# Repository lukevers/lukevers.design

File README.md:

# lukevers.design

There isn't a ton here right now. Feel free to poke around, but best to come back later.

✨

## Project Structure

Each project in [projects](./projects) should have a `manifest.json` that defines everything about the project. This data will be consumed on boot by the backend server, and be available via API for the frontend to consume.

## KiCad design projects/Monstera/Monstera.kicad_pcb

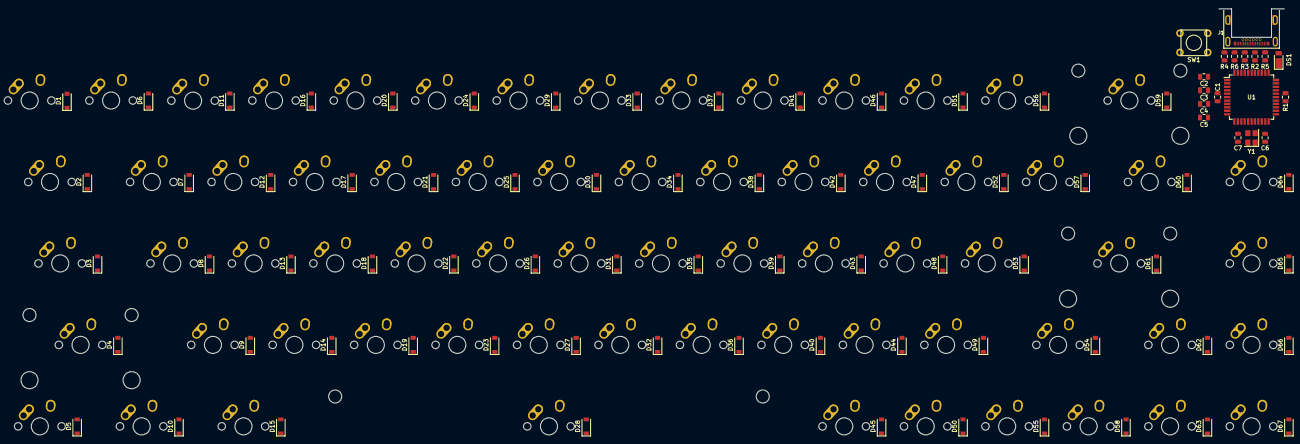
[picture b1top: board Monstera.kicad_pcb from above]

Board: 2 copper layers, 152 parts (0 on the bottom side), 100 nets, no tracks yet.

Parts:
C1: 1uF; C_0805_2012Metric
C2: 10uF; C_0805_2012Metric
C3, C4, C5: 0.1uF; C_0805_2012Metric
C6, C7: 22pF; C_0805_2012Metric
D1, D2, D3, D4, D5, D6, D7, D8, D9, D10, D11, D12, D13, D14, D15, D16, D17, D18, D19, D20, D21, D22, D23, D24, D25, D26, D27, D28, D29, D30, D31, D32, D33, D34, D35, D36, D37, D38, D39, D40, D41, D42, D43, D44, D45, D46, D47, D48, D49, D50, D51, D52, D53, D54, D55, D56, D57, D58, D59, D60, D61, D62, D63, D64, D65, D66, D67: D_Small; D_SOD-123
DS1: D_Schottky_Small; D_PowerDI-123
J1: USB_C_Receptacle; CX70M-24P1
MX_1, MX_2, MX_3, MX_4, MX_5, MX_6, MX_7, MX_8, MX_9, MX_10: MX-NoLED; MX-1U-NoLED
MX_A1: MX-NoLED; MX-1U-NoLED
MX_B1: MX-NoLED; MX-1U-NoLED
MX_BACKSPACE1: MX-NoLED; MX-2U-NoLED
MX_C1: MX-NoLED; MX-1U-NoLED
MX_COLON1: MX-NoLED; MX-1U-NoLED
MX_COMMA1: MX-NoLED; MX-1U-NoLED
MX_CTRL1: MX-NoLED; MX-1.25U-NoLED
MX_D1: MX-NoLED; MX-1U-NoLED
MX_DASH1: MX-NoLED; MX-1U-NoLED
MX_DOWN1: MX-NoLED; MX-1U-NoLED
MX_E1: MX-NoLED; MX-1U-NoLED
MX_ENTER1: MX-NoLED; MX-2.25U-NoLED
MX_ESC1: MX-NoLED; MX-1U-NoLED
MX_F1: MX-NoLED; MX-1U-NoLED
MX_FN1: MX-NoLED; MX-1U-NoLED
MX_G1: MX-NoLED; MX-1U-NoLED
MX_H1: MX-NoLED; MX-1U-NoLED
MX_HOME1: MX-NoLED; MX-1U-NoLED
MX_I1: MX-NoLED; MX-1U-NoLED
MX_J1: MX-NoLED; MX-1U-NoLED
MX_K1: MX-NoLED; MX-1U-NoLED
MX_L1: MX-NoLED; MX-1U-NoLED
MX_LALT1: MX-NoLED; MX-1.25U-NoLED
MX_LBRACE1: MX-NoLED; MX-1U-NoLED
MX_LEFT1: MX-NoLED; MX-1U-NoLED
MX_LMETA1: MX-NoLED; MX-1.25U-NoLED
MX_LOCK1: MX-NoLED; MX-1.75U-NoLED
MX_LSHIFT1: MX-NoLED; MX-2.25U-NoLED
MX_M1: MX-NoLED; MX-1U-NoLED
MX_N1: MX-NoLED; MX-1U-NoLED
MX_O1: MX-NoLED; MX-1U-NoLED
MX_P1: MX-NoLED; MX-1U-NoLED
MX_PERIOD1: MX-NoLED; MX-1U-NoLED
MX_PGDN1: MX-NoLED; MX-1U-NoLED
MX_PGUP1: MX-NoLED; MX-1U-NoLED
MX_PIPE1: MX-NoLED; MX-1.5U-NoLED
MX_PLUS1: MX-NoLED; MX-1U-NoLED
MX_Q1: MX-NoLED; MX-1U-NoLED
MX_QUEST1: MX-NoLED; MX-1U-NoLED
MX_QUOTE1: MX-NoLED; MX-1U-NoLED
MX_R1: MX-NoLED; MX-1U-NoLED
MX_RALT1: MX-NoLED; MX-1U-NoLED
MX_RBRACE1: MX-NoLED; MX-1U-NoLED
MX_RIGHT1: MX-NoLED; MX-1U-NoLED
MX_RMETA1: MX-NoLED; MX-1U-NoLED
MX_RSHIFT1: MX-NoLED; MX-1.75U-NoLED
MX_S1: MX-NoLED; MX-1U-NoLED
MX_SPACE1: MX-NoLED; MX-6.25U-NoLED
MX_T1: MX-NoLED; MX-1U-NoLED
MX_TAB1: MX-NoLED; MX-1.5U-NoLED
MX_U1: MX-NoLED; MX-1U-NoLED
MX_UP1: MX-NoLED; MX-1U-NoLED
MX_V1: MX-NoLED; MX-1U-NoLED
MX_W1: MX-NoLED; MX-1U-NoLED
MX_X1: MX-NoLED; MX-1U-NoLED
MX_Y1: MX-NoLED; MX-1U-NoLED
MX_Z1: MX-NoLED; MX-1U-NoLED
R1, R4: 10k; R_0805_2012Metric
R2, R3: 22; R_0805_2012Metric
R5, R6: 5k1; R_0805_2012Metric
SW1: SW_Push; PushButton_6x6mm_TH
U1: ATmega32U4-AU; TQFP-44_10x10mm_P0.8mm
Y1: 16MHz; Crystal_SMD_3225-4Pin_3.2x2.5mm

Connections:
+5V: C2.1, C3.1, C4.1, C5.1, R4.1, U1.2, U1.7, U1.14, U1.24, U1.34, U1.44
COL0: MX_CTRL1.1, MX_ESC1.1, MX_LOCK1.1, MX_LSHIFT1.1, MX_TAB1.1
COL1: MX_1.1, MX_A1.1, MX_LALT1.1, MX_Q1.1, MX_Z1.1
COL2: MX_2.1, MX_LMETA1.1, MX_S1.1, MX_W1.1, MX_X1.1
COL3: MX_3.1, MX_C1.1, MX_D1.1, MX_E1.1
COL4: MX_4.1, MX_F1.1, MX_R1.1, MX_V1.1
COL5: MX_5.1, MX_B1.1, MX_G1.1, MX_SPACE1.1, MX_T1.1
COL6: MX_6.1, MX_H1.1, MX_N1.1, MX_Y1.1
COL7: MX_7.1, MX_J1.1, MX_M1.1, MX_U1.1
COL8: MX_8.1, MX_COMMA1.1, MX_I1.1, MX_K1.1, MX_RMETA1.1
COL9: MX_9.1, MX_L1.1, MX_O1.1, MX_PERIOD1.1, MX_RALT1.1
COL10: MX_10.1, MX_COLON1.1, MX_FN1.1, MX_P1.1, MX_QUEST1.1
COL11: MX_DASH1.1, MX_LBRACE1.1, MX_LEFT1.1, MX_QUOTE1.1, MX_RSHIFT1.1
COL12: MX_DOWN1.1, MX_ENTER1.1, MX_PLUS1.1, MX_RBRACE1.1, MX_UP1.1
COL13: MX_BACKSPACE1.1, MX_HOME1.1, MX_PGDN1.1, MX_PGUP1.1, MX_PIPE1.1, MX_RIGHT1.1
GND: C1.2, C2.2, C3.2, C4.2, C5.2, C6.2, C7.2, J1.A1, J1.A12, J1.B1, J1.B12, J1.S1, R1.1, R5.1, R6.1, SW1.1, U1.5, U1.15, U1.23, U1.35, U1.43, Y1.2, Y1.4
unnamed: C1.1, U1.6
unnamed: C6.1, U1.17, Y1.1
unnamed: C7.1, U1.16, Y1.3
unnamed: D1.2, MX_ESC1.2
unnamed: D2.2, MX_TAB1.2
unnamed: D3.2, MX_LOCK1.2
unnamed: D4.2, MX_LSHIFT1.2
unnamed: D5.2, MX_CTRL1.2
unnamed: D6.2, MX_1.2
unnamed: D7.2, MX_Q1.2
unnamed: D8.2, MX_A1.2
unnamed: D9.2, MX_Z1.2
unnamed: D10.2, MX_LALT1.2
unnamed: D11.2, MX_2.2
unnamed: D12.2, MX_W1.2
unnamed: D13.2, MX_S1.2
unnamed: D14.2, MX_X1.2
unnamed: D15.2, MX_LMETA1.2
unnamed: D16.2, MX_3.2
unnamed: D17.2, MX_E1.2
unnamed: D18.2, MX_D1.2
unnamed: D19.2, MX_C1.2
unnamed: D20.2, MX_4.2
unnamed: D21.2, MX_R1.2
unnamed: D22.2, MX_F1.2
unnamed: D23.2, MX_V1.2
unnamed: D24.2, MX_5.2
unnamed: D25.2, MX_T1.2
unnamed: D26.2, MX_G1.2
unnamed: D27.2, MX_B1.2
unnamed: D28.2, MX_SPACE1.2
unnamed: D29.2, MX_6.2
unnamed: D30.2, MX_Y1.2
unnamed: D31.2, MX_H1.2
unnamed: D32.2, MX_N1.2
unnamed: D33.2, MX_7.2
unnamed: D34.2, MX_U1.2
unnamed: D35.2, MX_J1.2
unnamed: D36.2, MX_M1.2
unnamed: D37.2, MX_8.2
unnamed: D38.2, MX_I1.2
unnamed: D39.2, MX_K1.2
unnamed: D40.2, MX_COMMA1.2
unnamed: D41.2, MX_9.2
unnamed: D42.2, MX_O1.2
unnamed: D43.2, MX_L1.2
unnamed: D44.2, MX_PERIOD1.2
unnamed: D45.2, MX_RMETA1.2
unnamed: D46.2, MX_10.2
unnamed: D47.2, MX_P1.2
unnamed: D48.2, MX_COLON1.2
unnamed: D49.2, MX_QUEST1.2
unnamed: D50.2, MX_RALT1.2
unnamed: D51.2, MX_DASH1.2
unnamed: D52.2, MX_LBRACE1.2
unnamed: D53.2, MX_QUOTE1.2
unnamed: D54.2, MX_RSHIFT1.2
unnamed: D55.2, MX_FN1.2
unnamed: D56.2, MX_PLUS1.2
unnamed: D57.2, MX_RBRACE1.2
unnamed: D58.2, MX_LEFT1.2
unnamed: D59.2, MX_BACKSPACE1.2
unnamed: D60.2, MX_PIPE1.2
unnamed: D61.2, MX_ENTER1.2
unnamed: D62.2, MX_UP1.2
unnamed: D63.2, MX_DOWN1.2
unnamed: D64.2, MX_HOME1.2
unnamed: D65.2, MX_PGUP1.2
unnamed: D66.2, MX_PGDN1.2
unnamed: D67.2, MX_RIGHT1.2
unnamed: J1.A5, R5.2
unnamed: J1.A6, J1.B6, R2.2
unnamed: J1.A7, J1.B7, R3.2
unnamed: J1.B5, R6.2
unnamed: R1.2, U1.33
unnamed: R2.1, U1.4
unnamed: R3.1, U1.3
unnamed: R4.2, SW1.2, U1.13
ROW0: D1.1, D6.1, D11.1, D16.1, D20.1, D24.1, D29.1, D33.1, D37.1, D41.1, D46.1, D51.1, D56.1, D59.1
ROW1: D2.1, D7.1, D12.1, D17.1, D21.1, D25.1, D30.1, D34.1, D38.1, D42.1, D47.1, D52.1, D57.1, D60.1, D64.1
ROW2: D3.1, D8.1, D13.1, D18.1, D22.1, D26.1, D31.1, D35.1, D39.1, D43.1, D48.1, D53.1, D61.1, D65.1
ROW3: D4.1, D9.1, D14.1, D19.1, D23.1, D27.1, D32.1, D36.1, D40.1, D44.1, D49.1, D54.1, D62.1, D66.1
ROW4: D5.1, D10.1, D15.1, D28.1, D45.1, D50.1, D55.1, D58.1, D63.1, D67.1
VBUS: DS1.2, J1.A4, J1.A9, J1.B4, J1.B9

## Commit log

2020-03-05 Pull data from endpoint
2020-03-06 Add error pages and split out post-load
2020-03-06 Cleanip
2020-03-06 Add backend server for hosting
2020-03-06 TBD README
2020-03-06 Move Monstera project here
2020-03-06 Load manifests from repository
2020-03-06 Return 404 on the /projects/*.json if not found
2020-03-07 Place everything
2020-03-07 Edge cuts!
2020-03-09 Move project
2020-03-09 Add base dir for Monstera MK
2020-03-09 Some basic PDP work
2020-03-09 Only preventDefault on links if they are a defined route
2020-03-09 Add json from keyboard-layout-editor.com
2020-03-09 Fix react key issue
2020-03-09 Fix styling issue for images
2020-03-09 Add basic nav
2020-03-09 Fix naming issue
2020-03-09 Some more work on the PDP
2020-03-09 Basic button example
2020-03-09 Add wrapper for padding on mobile
2020-03-09 Beginning work to support tags and collections
2020-03-10 Tag/collection pages
2020-03-10 Add basic dockerfile
2020-03-11 Force a name in the Dockerfile
2020-03-11 Add desp
2020-03-11 Add node sass
2020-03-11 Add public css dir
2020-03-11 Shorten index.html
2020-03-11 No node sass global
2020-03-11 Add "app" binary to gitignore
2020-03-11 Switch favicon out
2020-03-11 Add svg, 256png + update readme
2020-03-11 Add 512 icon and scale down in README
2020-03-11 Add deploy.sh to be lazy af
2020-03-11 Add chmod x
2020-03-11 Fix param order
2020-03-11 Add a go away note, and fix param order
2020-03-12 Fix bug with pointer-events on children of anchor tags
2020-03-12 More PDP elements
2020-03-12 "SalablE" with false defaults
2020-03-17 Basic pill homepage
2020-03-24 Visible bool for projects
2020-06-07 Bump websocket-extensions from 0.1.3 to 0.1.4
    Bumps [websocket-extensions](https://github.com/faye/websocket-extensions-node) from 0.1.3 to 0.1.4.
    - [Release notes](https://github.com/faye/websocket-extensions-node/releases)
    - [Changelog](https://github.com/faye/websocket-extensions-node/blob/master/CHANGELOG.md)
    - [Commits](https://github.com/faye/websocket-extensions-node/compare/0.1.3...0.1.4)
2020-07-19 Bump lodash from 4.17.15 to 4.17.19
    Bumps [lodash](https://github.com/lodash/lodash) from 4.17.15 to 4.17.19.
    - [Release notes](https://github.com/lodash/lodash/releases)
    - [Commits](https://github.com/lodash/lodash/compare/4.17.15...4.17.19)
2020-08-01 Bump elliptic from 6.5.2 to 6.5.3
    Bumps [elliptic](https://github.com/indutny/elliptic) from 6.5.2 to 6.5.3.
    - [Release notes](https://github.com/indutny/elliptic/releases)
    - [Commits](https://github.com/indutny/elliptic/compare/v6.5.2...v6.5.3)
2020-11-25 Bump highlight.js from 9.18.0 to 10.1.2
    Bumps [highlight.js](https://github.com/highlightjs/highlight.js) from 9.18.0 to 10.1.2.
    - [Release notes](https://github.com/highlightjs/highlight.js/releases)
    - [Changelog](https://github.com/highlightjs/highlight.js/blob/10.1.2/CHANGES.md)
    - [Commits](https://github.com/highlightjs/highlight.js/compare/9.18.0...10.1.2)
2020-12-04 Bump highlight.js from 9.18.0 to 10.4.1
    Bumps [highlight.js](https://github.com/highlightjs/highlight.js) from 9.18.0 to 10.4.1.
    - [Release notes](https://github.com/highlightjs/highlight.js/releases)
    - [Changelog](https://github.com/highlightjs/highlight.js/blob/master/CHANGES.md)
    - [Commits](https://github.com/highlightjs/highlight.js/compare/9.18.0...10.4.1)
2020-12-12 Bump ini from 1.3.5 to 1.3.8
    Bumps [ini](https://github.com/isaacs/ini) from 1.3.5 to 1.3.8.
    - [Release notes](https://github.com/isaacs/ini/releases)
    - [Commits](https://github.com/isaacs/ini/compare/v1.3.5...v1.3.8)
2021-03-10 Bump elliptic from 6.5.2 to 6.5.4
    Bumps [elliptic](https://github.com/indutny/elliptic) from 6.5.2 to 6.5.4.
    - [Release notes](https://github.com/indutny/elliptic/releases)
    - [Commits](https://github.com/indutny/elliptic/compare/v6.5.2...v6.5.4)
2021-03-31 Bump y18n from 3.2.1 to 3.2.2
    Bumps [y18n](https://github.com/yargs/y18n) from 3.2.1 to 3.2.2.
    - [Release notes](https://github.com/yargs/y18n/releases)
    - [Changelog](https://github.com/yargs/y18n/blob/master/CHANGELOG.md)
    - [Commits](https://github.com/yargs/y18n/commits)
2021-05-07 Bump ua-parser-js from 0.7.21 to 0.7.28
    Bumps [ua-parser-js](https://github.com/faisalman/ua-parser-js) from 0.7.21 to 0.7.28.
    - [Release notes](https://github.com/faisalman/ua-parser-js/releases)
    - [Commits](https://github.com/faisalman/ua-parser-js/compare/0.7.21...0.7.28)
2021-05-09 Bump url-parse from 1.4.7 to 1.5.1
    Bumps [url-parse](https://github.com/unshiftio/url-parse) from 1.4.7 to 1.5.1.
    - [Release notes](https://github.com/unshiftio/url-parse/releases)
    - [Commits](https://github.com/unshiftio/url-parse/compare/1.4.7...1.5.1)
2021-05-11 Bump lodash from 4.17.15 to 4.17.21
    Bumps [lodash](https://github.com/lodash/lodash) from 4.17.15 to 4.17.21.
    - [Release notes](https://github.com/lodash/lodash/releases)
    - [Commits](https://github.com/lodash/lodash/compare/4.17.15...4.17.21)
2021-05-11 Bump hosted-git-info from 2.8.8 to 2.8.9
    Bumps [hosted-git-info](https://github.com/npm/hosted-git-info) from 2.8.8 to 2.8.9.
    - [Release notes](https://github.com/npm/hosted-git-info/releases)
    - [Changelog](https://github.com/npm/hosted-git-info/blob/v2.8.9/CHANGELOG.md)
    - [Commits](https://github.com/npm/hosted-git-info/compare/v2.8.8...v2.8.9)
2021-05-26 Bump browserslist from 4.9.1 to 4.16.6
    Bumps [browserslist](https://github.com/browserslist/browserslist) from 4.9.1 to 4.16.6.
    - [Release notes](https://github.com/browserslist/browserslist/releases)
    - [Changelog](https://github.com/browserslist/browserslist/blob/main/CHANGELOG.md)
    - [Commits](https://github.com/browserslist/browserslist/compare/4.9.1...4.16.6)
